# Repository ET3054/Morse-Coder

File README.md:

# Morse-Coder

Kurs:                   ET3054 Entwurf und Fertigung von Flachbaugruppen

Jahrgang:               2024

Gruppe:                 8

Teilnehmer:             Hendrik Stadler, Jasper Martin Kyeck, Sebastian Gust

Projekt:                Morse-Coder

Beschreibung:           Eingabe von Morse-Code mit auditivem Feedback und Übersetzung auf LCD-Display, Eingabe von Buchstaben/Wörtern über Dreh-Encoder (Joystick) und Übersetzung als auditiven Sound in Morse-Code
                        mögliche Erweiterung -> Training und Übungen für Encoding und Decoding von Morse-Code

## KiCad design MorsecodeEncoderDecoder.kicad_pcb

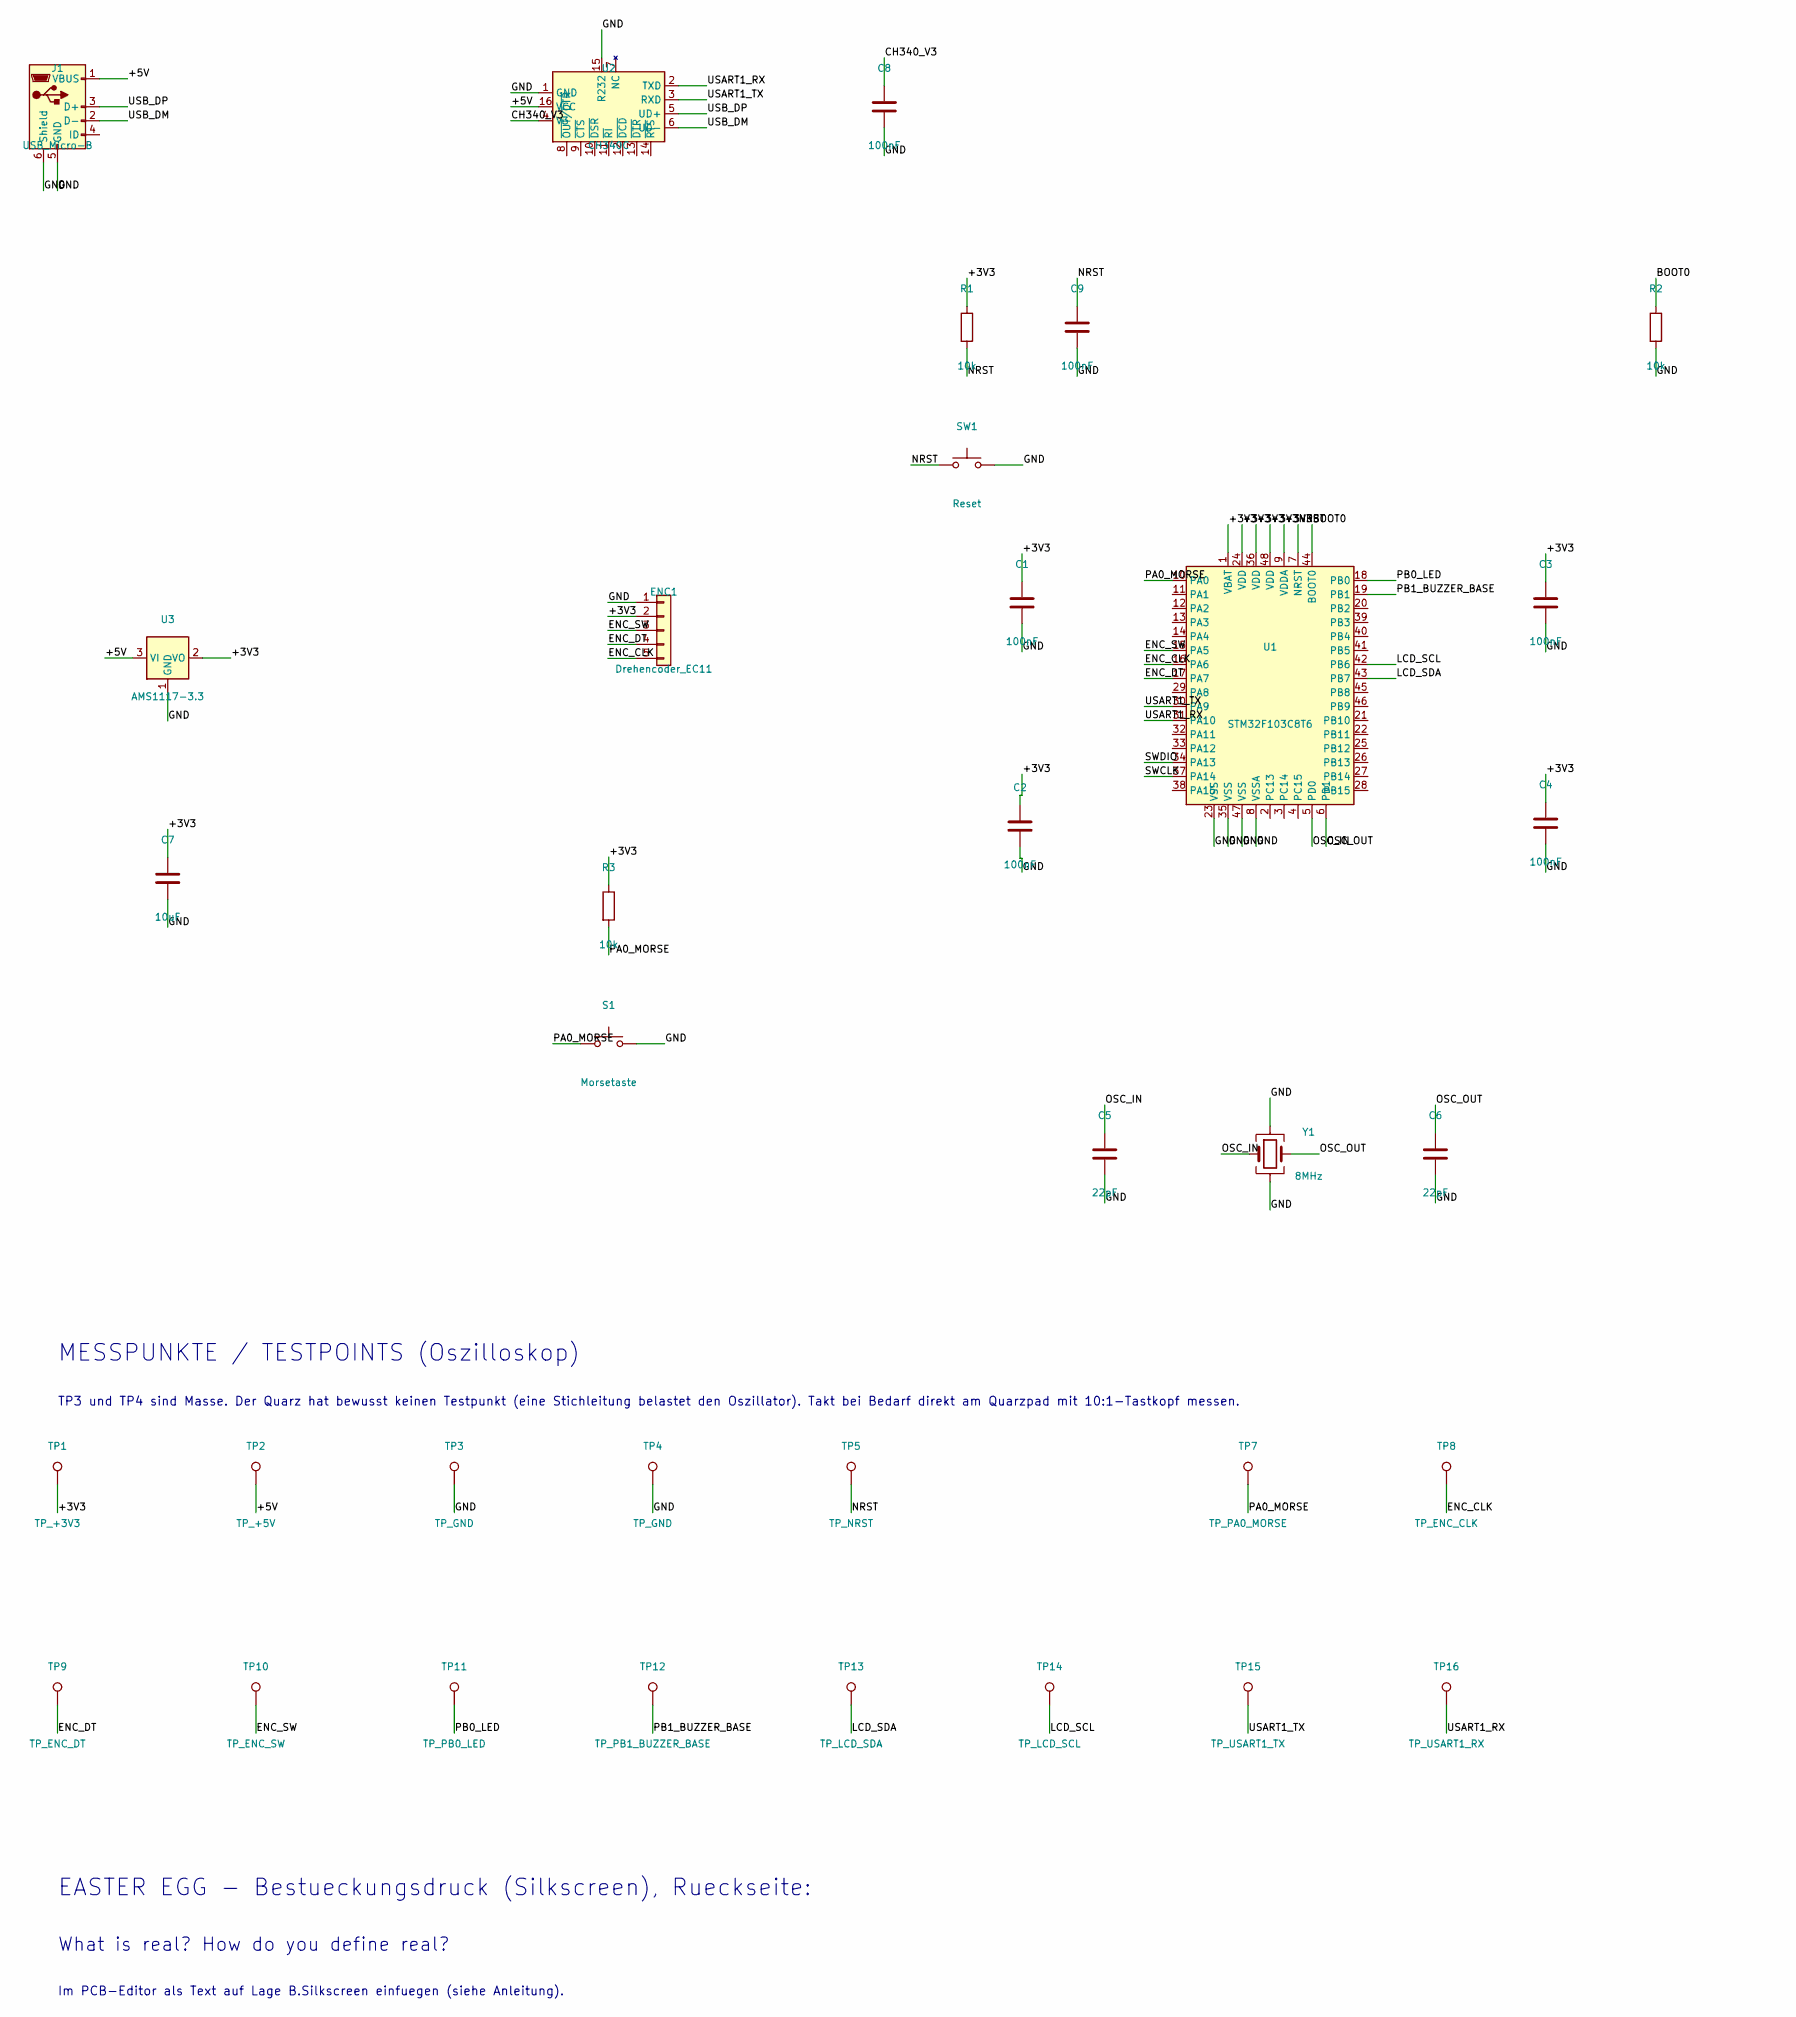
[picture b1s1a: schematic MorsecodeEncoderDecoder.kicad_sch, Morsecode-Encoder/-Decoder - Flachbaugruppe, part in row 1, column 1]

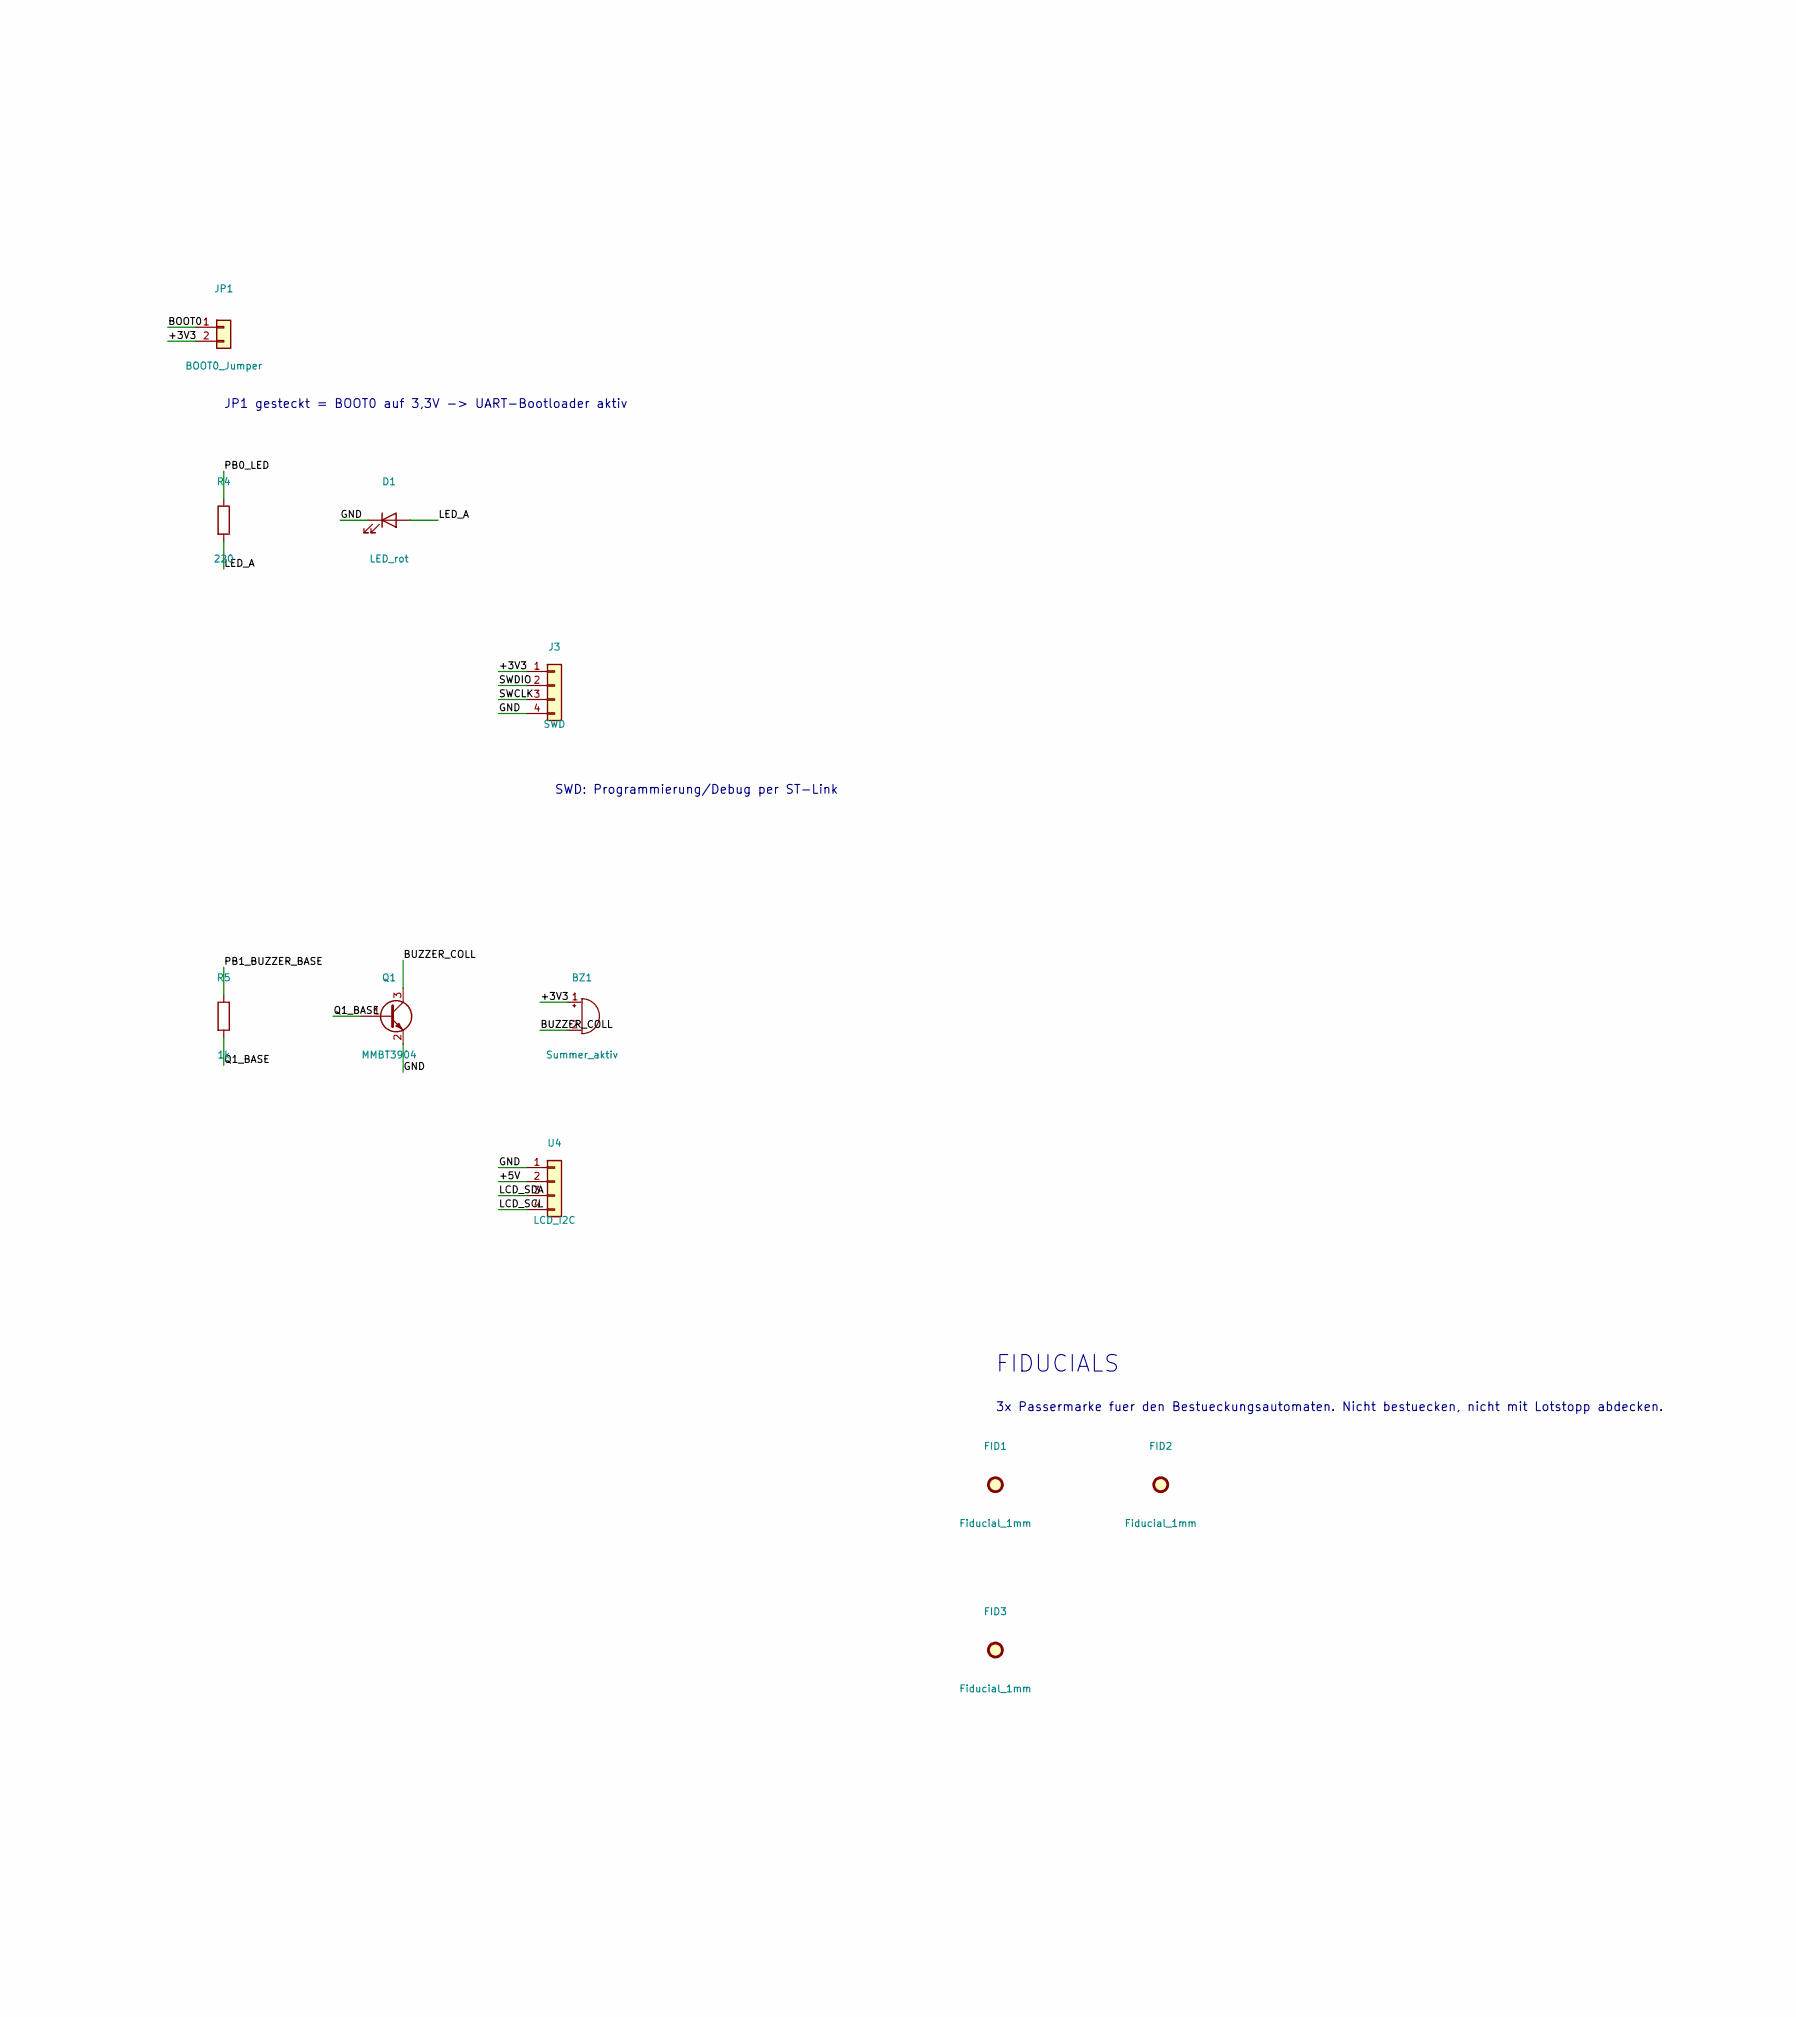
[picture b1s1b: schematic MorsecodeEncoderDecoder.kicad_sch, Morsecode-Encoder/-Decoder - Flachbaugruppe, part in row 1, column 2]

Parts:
BZ1: Summer_aktiv; Buzzer_12x9.5RM7.6; LCSC PRUEFEN
C1, C2, C3, C4, C8, C9: 100nF; C_0805_2012Metric; LCSC C49678
C5, C6: 22pF; C_0805_2012Metric; LCSC PRUEFEN
C7: 10uF; C_0805_2012Metric; LCSC C15850
D1: LED_rot; LED_0805_2012Metric; LCSC PRUEFEN
ENC1: Drehencoder_EC11; PinHeader_1x05_P2.54mm_Vertical; LCSC PRUEFEN
FID1, FID2, FID3: Fiducial_1mm; Fiducial_1mm_Mask2mm
J1: USB_Micro-B; USB_Micro-B_Molex-105017-0001; LCSC PRUEFEN
J3: SWD; PinHeader_1x04_P2.54mm_Vertical; LCSC PRUEFEN
JP1: BOOT0_Jumper; PinHeader_1x02_P2.54mm_Vertical; LCSC PRUEFEN
Q1: MMBT3904; SOT-23; LCSC PRUEFEN
R1, R2, R3: 10k; R_0805_2012Metric; LCSC C17414
R4: 220; R_0805_2012Metric; LCSC PRUEFEN
R5: 1k; R_0805_2012Metric; LCSC PRUEFEN
S1: Morsetaste; SW_SPST_TL3342; LCSC PRUEFEN
SW1: Reset; SW_SPST_TL3342; LCSC PRUEFEN
TP1: TP_+3V3; TestPoint_Pad_D1.5mm
TP2: TP_+5V; TestPoint_Pad_D1.5mm
TP3, TP4: TP_GND; TestPoint_Pad_D1.5mm
TP5: TP_NRST; TestPoint_Pad_D1.5mm
TP7: TP_PA0_MORSE; TestPoint_Pad_D1.5mm
TP8: TP_ENC_CLK; TestPoint_Pad_D1.5mm
TP9: TP_ENC_DT; TestPoint_Pad_D1.5mm
TP10: TP_ENC_SW; TestPoint_Pad_D1.5mm
TP11: TP_PB0_LED; TestPoint_Pad_D1.5mm
TP12: TP_PB1_BUZZER_BASE; TestPoint_Pad_D1.5mm
TP13: TP_LCD_SDA; TestPoint_Pad_D1.5mm
TP14: TP_LCD_SCL; TestPoint_Pad_D1.5mm
TP15: TP_USART1_TX; TestPoint_Pad_D1.5mm
TP16: TP_USART1_RX; TestPoint_Pad_D1.5mm
U1: STM32F103C8T6; LQFP-48_7x7mm_P0.5mm; LCSC C8734
U2: CH340C; SOIC-16_3.9x9.9mm_P1.27mm; LCSC C84681
U3: AMS1117-3.3; SOT-223-3_TabPin2; LCSC C6186
U4: LCD_I2C; PinHeader_1x04_P2.54mm_Vertical; LCSC PRUEFEN
Y1: 8MHz; Crystal_SMD_3225-4Pin_3.2x2.5mm; LCSC PRUEFEN

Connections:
/+3V3: BZ1.1 (+), C1.1, C2.1, C3.1, C4.1, C7.1, ENC1.2, J3.1, JP1.2, R1.1, R3.1, TP1.1 (1_1), U1.1 (VBAT), U1.9 (VDDA), U1.24 (VDD), U1.36 (VDD), U1.48 (VDD), U3.2 (VO)
/+5V: J1.1 (VBUS), TP2.1 (1_1), U2.16 (VCC), U3.3 (VI), U4.2
/BOOT0: JP1.1, R2.1, U1.44 (BOOT0)
/BUZZER_COLL: BZ1.2 (-), Q1.3 (C)
/CH340_V3: C8.1, U2.4 (V3)
/ENC_CLK: ENC1.5, TP8.1 (1_1), U1.16 (PA6)
/ENC_DT: ENC1.4, TP9.1 (1_1), U1.17 (PA7)
/ENC_SW: ENC1.3, TP10.1 (1_1), U1.15 (PA5)
/GND: C1.2, C2.2, C3.2, C4.2, C5.2, C6.2, C7.2, C8.2, C9.2, D1.1 (K), ENC1.1, J1.5 (GND), J1.6 (Shield), J3.4, Q1.2 (E), R2.2, S1.2, SW1.2, TP3.1 (1_1), TP4.1 (1_1), U1.8 (VSSA), U1.23 (VSS), U1.35 (VSS), U1.47 (VSS), U2.1 (GND), U2.15 (R232), U3.1 (GND), U4.1, Y1.2, Y1.4
/LCD_SCL: TP14.1 (1_1), U1.42 (PB6), U4.4
/LCD_SDA: TP13.1 (1_1), U1.43 (PB7), U4.3
/LED_A: D1.2 (A), R4.2
/NRST: C9.1, R1.2, SW1.1, TP5.1 (1_1), U1.7 (NRST)
/OSC_IN: C5.1, U1.5 (PD0), Y1.1
/OSC_OUT: C6.1, U1.6 (PD1), Y1.3
/PA0_MORSE: R3.2, S1.1, TP7.1 (1_1), U1.10 (PA0)
/PB0_LED: R4.1, TP11.1 (1_1), U1.18 (PB0)
/PB1_BUZZER_BASE: R5.1, TP12.1 (1_1), U1.19 (PB1)
/Q1_BASE: Q1.1 (B), R5.2
/SWCLK: J3.3, U1.37 (PA14)
/SWDIO: J3.2, U1.34 (PA13)
/USART1_RX: TP16.1 (1_1), U1.31 (PA10), U2.2 (TXD)
/USART1_TX: TP15.1 (1_1), U1.30 (PA9), U2.3 (RXD)
/USB_DM: J1.2 (D-), U2.6 (UD-)
/USB_DP: J1.3 (D+), U2.5 (UD+)

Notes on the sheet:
What is real? How do you define real?
MESSPUNKTE / TESTPOINTS (Oszilloskop)
3x Passermarke fuer den Bestueckungsautomaten. Nicht bestuecken, nicht mit Lotstopp abdecken.
SWD: Programmierung/Debug per ST-Link
EASTER EGG - Bestueckungsdruck (Silkscreen), Rueckseite:
JP1 gesteckt = BOOT0 auf 3,3V -> UART-Bootloader aktiv
TP3 und TP4 sind Masse. Der Quarz hat bewusst keinen Testpunkt (eine Stichleitung belastet den Oszillator). Takt bei Bedarf direkt am Quarzpad mit 10:1-Tastkopf messen.
Im PCB-Editor als Text auf Lage B.Silkscreen einfuegen (siehe Anleitung).
FIDUCIALS

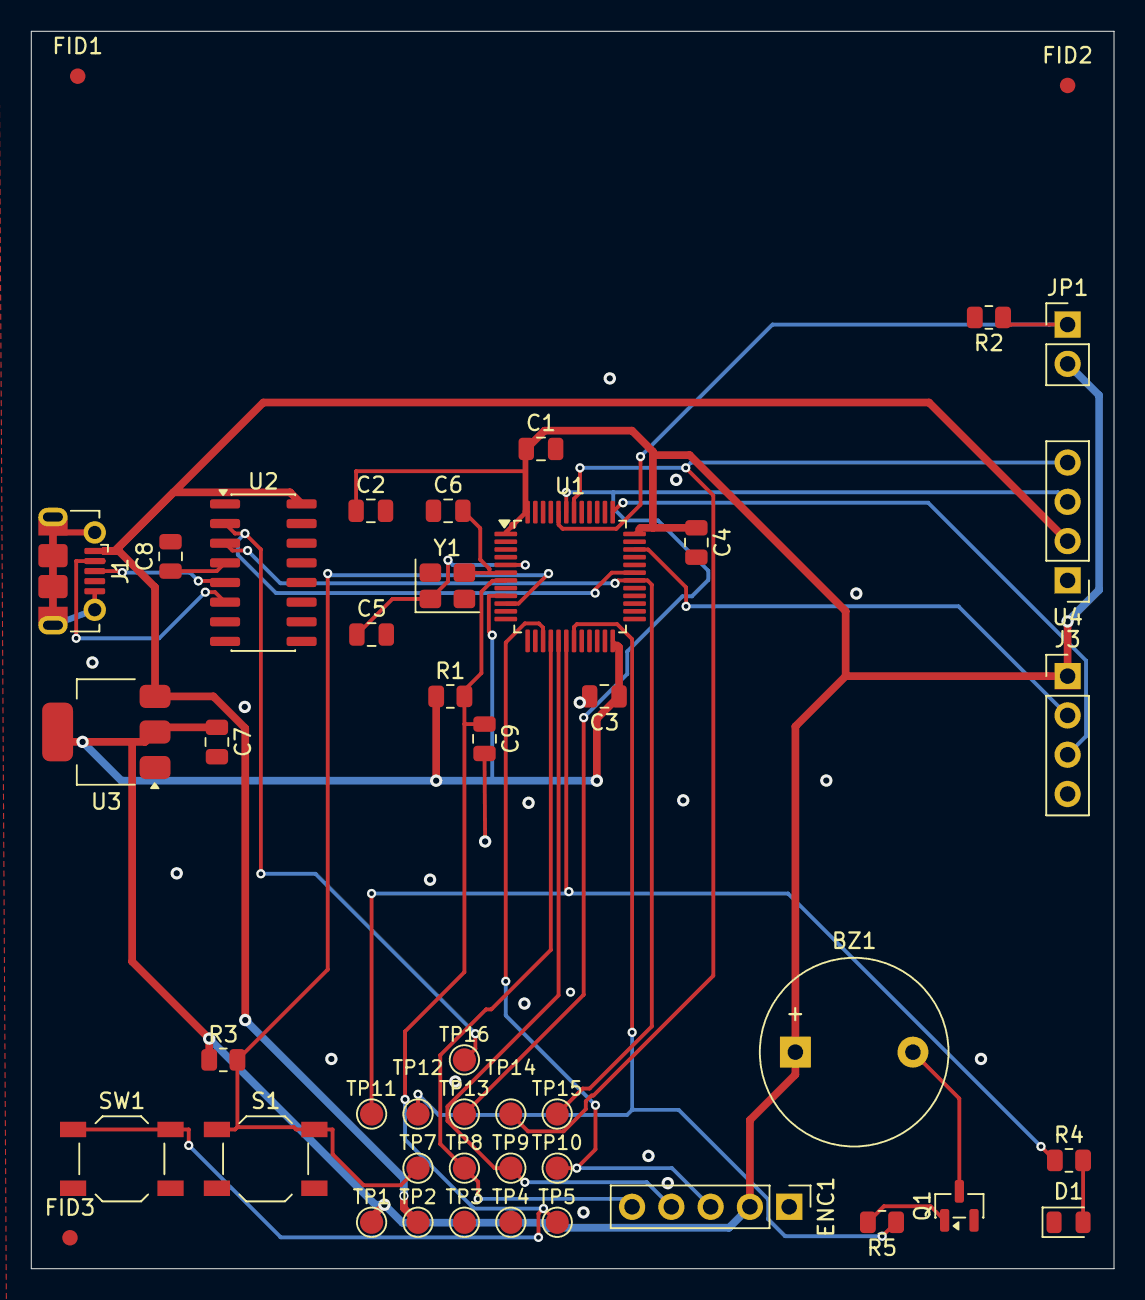
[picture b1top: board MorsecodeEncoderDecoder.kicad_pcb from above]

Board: 2 copper layers, 70.0 x 80.0 mm, 46 parts (0 on the bottom side), 25 nets.

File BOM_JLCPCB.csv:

Comment,Designator,Footprint,LCSC Part Number,Menge,Hinweis / Auswahlkriterium
Summer_aktiv,BZ1,Buzzer_Beeper:Buzzer_12x9.5RM7.6,PRUEFEN,1,"Aktiver Summer 3.3V, THT RM7.6"
100nF,"C1,C2,C3,C4,C8",Capacitor_SMD:C_0805_2012Metric,C49678,5,100nF 0805 X7R
22pF,"C5,C6",Capacitor_SMD:C_0805_2012Metric,PRUEFEN,2,22pF 0805 C0G/NP0
10uF,C7,Capacitor_SMD:C_0805_2012Metric,C15850,1,10uF 0805 MLCC
LED_rot,D1,LED_SMD:LED_0805_2012Metric,PRUEFEN,1,LED 0805 rot
Drehencoder_EC11,ENC1,Connector_PinHeader_2.54mm:PinHeader_1x05_P2.54mm_Vertical,PRUEFEN,1,Stiftleiste 1x05 RM2.54 fuer KY-040 / EC11 Modul
USB_Micro-B,J1,Connector_USB:USB_Micro-B_Molex-105017-0001,PRUEFEN,1,"USB Micro-B Buchse SMD, Molex 105017-0001 kompatibel"
SWD,J3,Connector_PinHeader_2.54mm:PinHeader_1x04_P2.54mm_Vertical,PRUEFEN,1,Stiftleiste 1x04 RM2.54 - ST-Link Anschluss
BOOT0_Jumper,JP1,Connector_PinHeader_2.54mm:PinHeader_1x02_P2.54mm_Vertical,PRUEFEN,1,Stiftleiste 1x02 RM2.54 - Jumper gesteckt = UART-Bootloader
MMBT3904,Q1,Package_TO_SOT_SMD:SOT-23,PRUEFEN,1,"MMBT3904 SOT-23 (NPN), Pinfolge B/E/C"
10k,"R1,R2,R3",Resistor_SMD:R_0805_2012Metric,C17414,3,10k 0805 1% (JLCPCB Basic)
220,R4,Resistor_SMD:R_0805_2012Metric,PRUEFEN,1,220R 0805 1%
1k,R5,Resistor_SMD:R_0805_2012Metric,PRUEFEN,1,1k 0805 1%
Morsetaste,S1,Button_Switch_SMD:SW_SPST_TL3342,PRUEFEN,1,Taster SMD oder externe Morsetaste ueber Loetpad
Reset,SW1,Button_Switch_SMD:SW_SPST_TL3342,PRUEFEN,1,Taster SMD 3.9x3.0mm
STM32F103C8T6,U1,Package_QFP:LQFP-48_7x7mm_P0.5mm,C8734,1,verifiziert (LCSC/JLCPCB)
CH340C,U2,Package_SO:SOIC-16_3.9x9.9mm_P1.27mm,C84681,1,"verifiziert (LCSC/JLCPCB), interner Takt - kein Quarz noetig"
AMS1117-3.3,U3,Package_TO_SOT_SMD:SOT-223-3_TabPin2,C6186,1,verifiziert (LCSC/JLCPCB)
LCD_I2C,U4,Connector_PinHeader_2.54mm:PinHeader_1x04_P2.54mm_Vertical,PRUEFEN,1,Stiftleiste 1x04 RM2.54 fuer 16x2 LCD mit PCF8574-Backpack
8MHz,Y1,Crystal:Crystal_SMD_3225-4Pin_3.2x2.5mm,PRUEFEN,1,"8MHz SMD 3225 4-Pad, 20ppm"
